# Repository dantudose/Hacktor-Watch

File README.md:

# Hacktor-Watch 2.0

Open-source power for apps, AI, and fearless hardware hacking!
Why just wear a smartwatch when you can hack it? Hacktor Watch 2.0 is your open-source playground on the wrist — powered by the dual-core ESP32-S3 with Wi-Fi and Bluetooth, rocking a bright 1.28" touch display, and loaded with goodies like a 6-axis IMU, mic, speaker, haptics, and fuel gauge. You get 32MB flash, 8MB PSRAM, USB-C charging, and a 200mAh LiPo to keep your creations running. Whether you’re building custom apps in Arduino or ESP-IDF, training tiny AI models, or turning it into a wearable IoT gadget, this is a smartwatch that’s down for any experiment you throw at it. 

And yes — it’s also sleek and stylish, so no matter how good or bad your code is, it will always look great on your wrist!

<div style='float:center'>
   
  </div>

## Hardware Diagram &amp; features

<a href="https://docs.google.com/drawings/d/1u0_o-W6L3w2xveMWQQGLrzZhusZ90oDN8ES3exkrWA4/edit?usp=sharing">Hardware diagram.</a>

This is a open-hardware wearable based on the ESP32 microcontroller. It is fully Arduino-compatible and it comes with the following features:
* <a href="https://www.espressif.com/sites/default/files/documentation/esp32-s3_datasheet_en.pdf">ESP32-S3</a> processor (dual-core 240MHz, WiFI, BLE, 512kB SRAM and 4MB Flash)
* <a href="https://www.aliexpress.com/item/1005007293053050.html">GC9A01</a> 1.28 inch color LCD, 240 x 240 pixels with CST816T capacitive touch screen
* <a href="https://www.st.com/en/mems-and-sensors/lsm6dsl.html">LSM6DSLTR</a> 6-axis inertial sensor (accelerometer and gyroscope)
* <a href="https://www.winbond.com/hq/product/code-storage-flash-memory/serial-nor-flash/?__locale=en&partNo=W25Q256JV">W25Q256JVEIQ</a> 32MB external SPI Flash
* <a href="https://cdn-shop.adafruit.com/product-files/4677/4677_esp-psram64_esp-psram64h_datasheet_en.pdf">ESP-PSRAM64H</a> 8MB PSRAM
* <a href="https://www.ti.com/product/DRV2605/part-details/DRV2605YZFR">DRV2605YZFR</a> haptic driver
* <a href="https://jlcpcb.com/api/file/downloadByFileSystemAccessId/8586212537977618432">LMD2718T261-OA1</a> microphone
* <a href="https://www.analog.com/media/en/technical-documentation/data-sheets/max98357a-max98357b.pdf">MAX98357</a> I2S audio amplifier and speaker
* <a href="https://www.analog.com/media/en/technical-documentation/data-sheets/max17048-max17049.pdf">MAX17048</a> fuel gauge
* Dual <a href="https://www.richtek.com/m/Products/Switching%20Regulators/Buck-Boost%20Converter/RT6160A?sc_lang=en">RT6160</a> DC/DC PMIC (main power and peripherals)
* <a href="https://www.ti.com/lit/ds/symlink/bq24040.pdf?ts=1754753213993">BQ24040</a> LiPo charger
* 200mAh LiPo battery
* USB-C connector for charging and data

<div id="cover">

</div>

## Repository Contents

* **/Hardware** - Schematic and hardware design files (Fusion360 & KiCAD)
* **/Images** - Images & diagrams
* **/Mechanical** - 3D files for the watch case

### Button Layout

 <div style='float:left'>
<table>
<thead>
  <tr>
    <th>Button</th>
    <th>ESP32 Pin</th>
  </tr></thead>
  <tbody>
  <tr>
    <td>BOOT</td>
    <td>IO0</td>
  </tr>
  <tr>
    <td>RESET</td>
    <td>EN</td>
  </tr>
  </tbody>
</table>
 </div>
<div style='float:right'>
   
  </div>

## Software Support
The watch supports Arduino and ESP-IDF programming. For a working NuttX port, check out <a href="https://github.com/radupascale/hectorwatch-nuttx">Radu Pascale's</a> repo. 

## License Information

HW design by <a href="https://github.com/radupascale">Radu Pascale</a>.

This product is _**open source**_! 

Please review the LICENSE file for license information. 

Distributed as-is; no warranty is given.

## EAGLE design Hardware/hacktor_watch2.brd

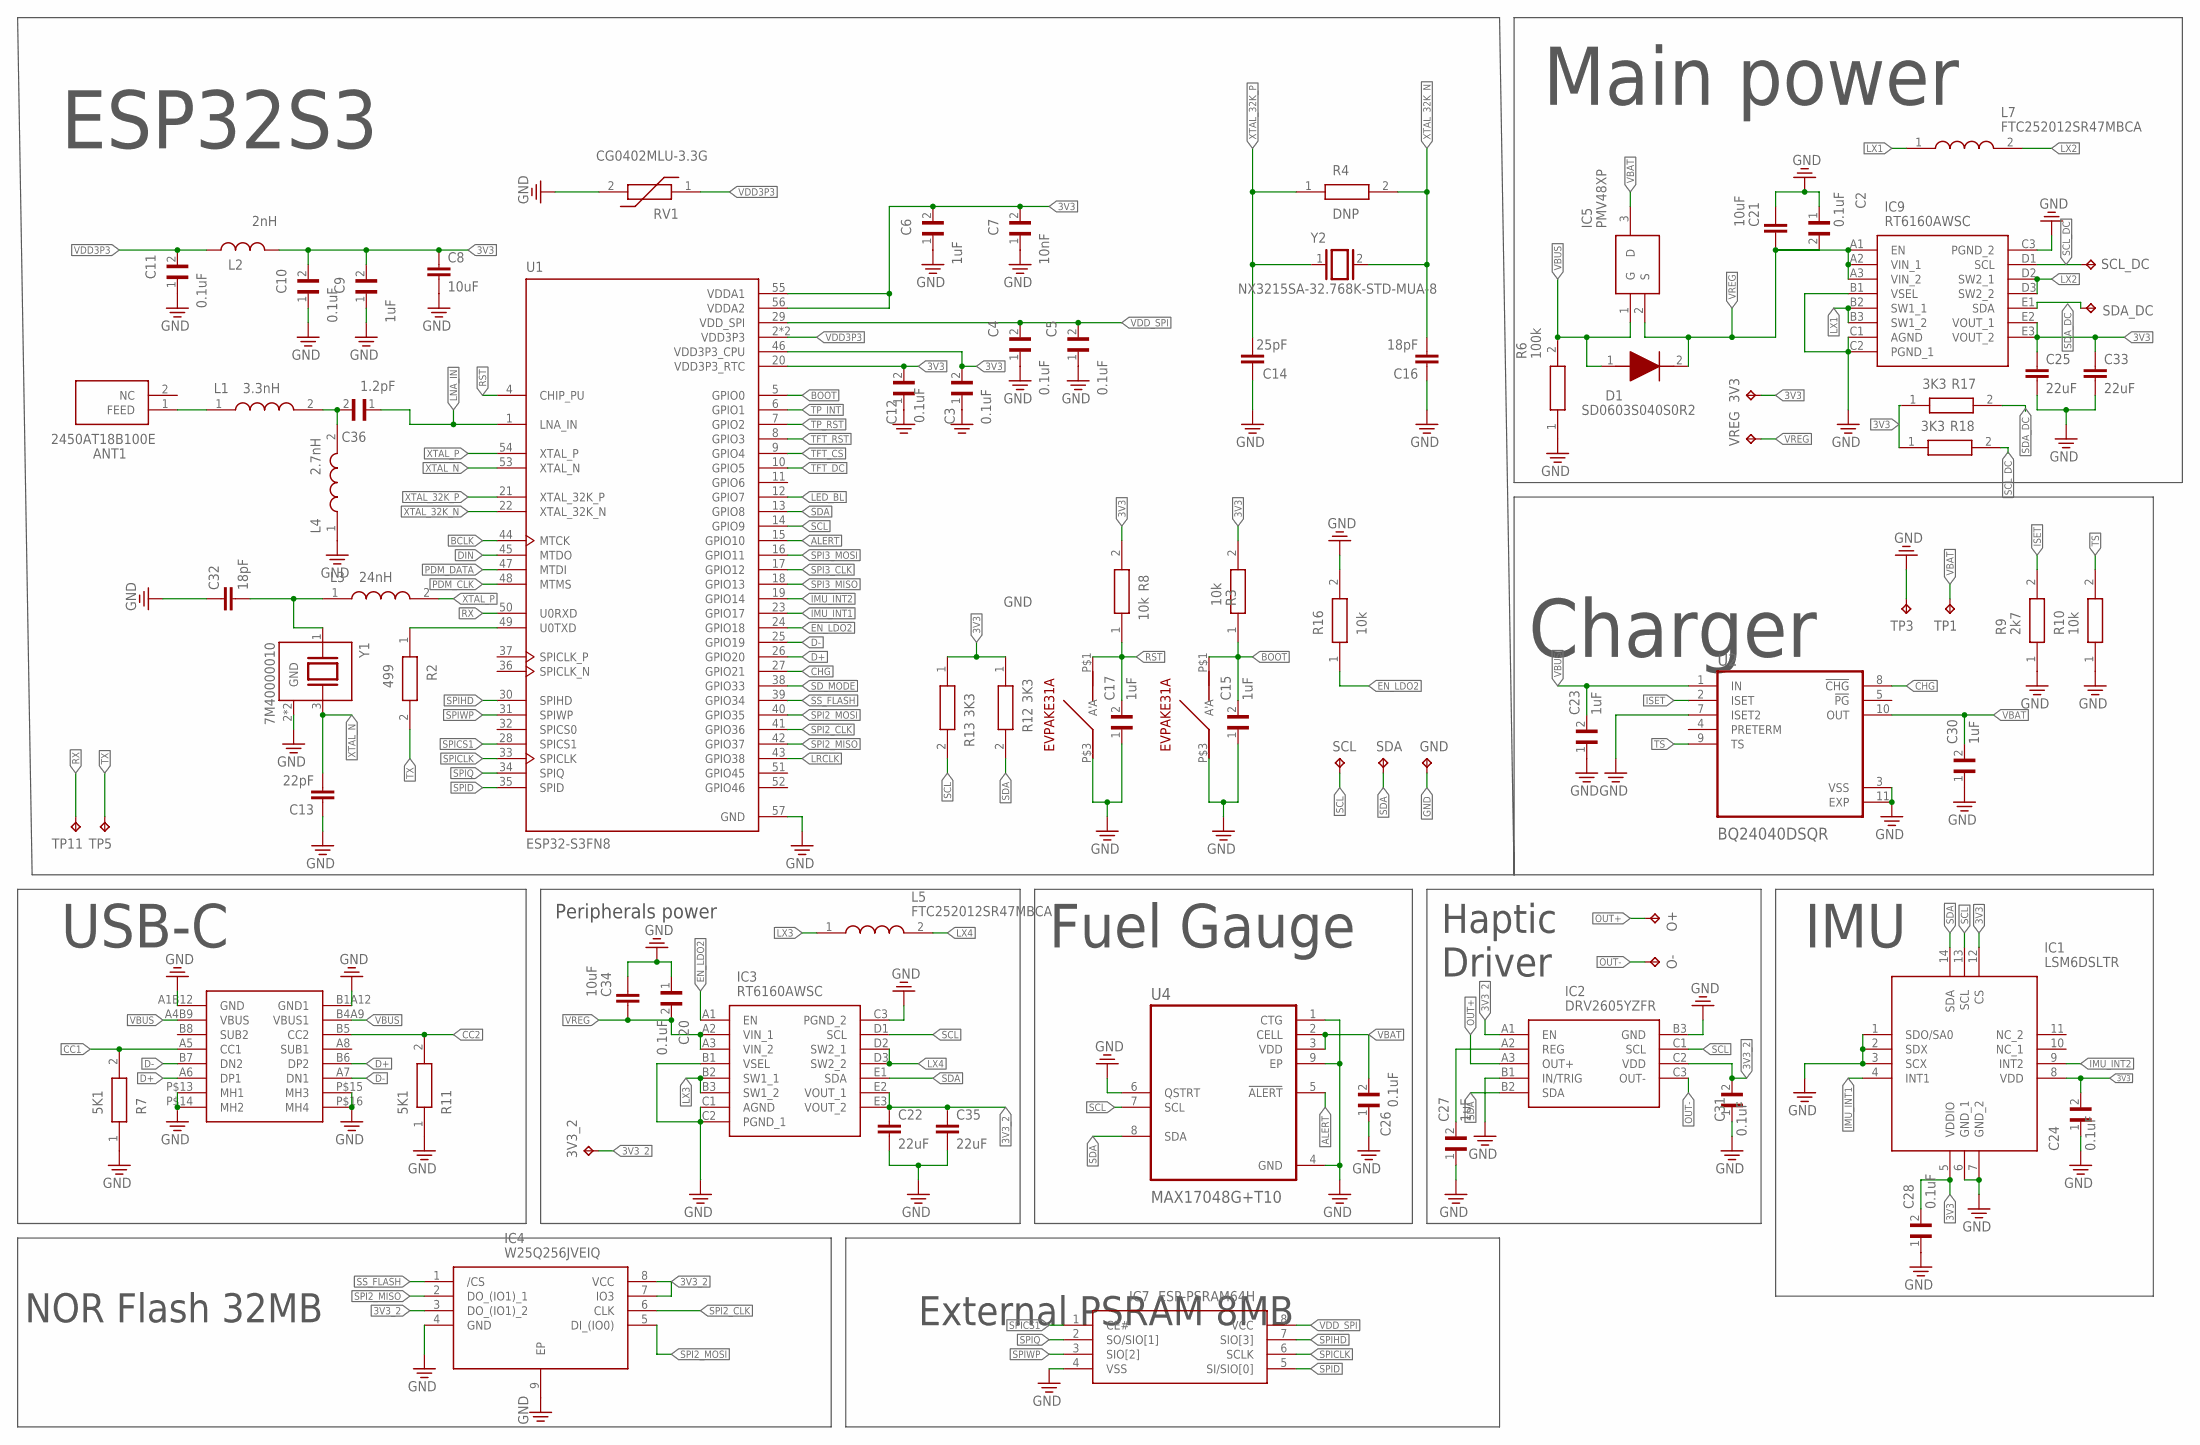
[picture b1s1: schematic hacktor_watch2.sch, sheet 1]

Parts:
3V3, 3V3_2: TPTP20R; TP20R
ANT1: 2450AT18B100E; ANTC3216X140N
C2, C3, C4, C5, C10, C11, C12, C20, C24, C26, C28, C31: 0.1uF; 0201
C6, C9, C15, C17, C23, C27, C30: 1uF; 0201
C7: 10nF; 0201
C8, C21, C34: 10uF; 0402
C13: 22pF; 0402
C14: 25pF; 0402
C16, C32: 18pF; 0402
C22, C25, C33, C35: 22uF; 0402
C36: 1.2pF; 0201
D1: SD0603S040S0R2; SD0603
GND: TPTP20R; TP20R
IC1: LSM6DSLTR
IC2: DRV2605YZFR; BGA9C50P3X3_144X144X62
IC3, IC9: RT6160AWSC; BGA15C40P3X5_140X230X60
IC4: W25Q256JVEIQ; SON127P800X600X80-9N
IC5: PMV48XP; SOT95P230X110-3N
IC7: ESP-PSRAM64H; SOIC127P600X175-8N
L1: 3.3nH; LQP15MN10NG02D
L2: 2nH; INDC1006X60N
L3: 24nH; LQP15MN10NG02D
L4: 2.7nH; LQP15MN10NG02D
L5, L7: FTC252012SR47MBCA; INDC2016X100N
O+: TPTP20R; TP20R
O-: TPTP20R; TP20R
R2: 499; 0201
R3, R8, R10, R16: 10k; 0201
R4: DNP; 0201
R6: 100k; 0201
R7, R11: 5K1; 0201
R9: 2k7; 0201
R12, R13, R17, R18: 3K3; 0201
RV1: CG0402MLU-3.3G; VARC1005X41N
SCL: TPTP20R; TP20R
SCL_DC: TPTP20R; TP20R
SDA: TPTP20R; TP20R
SDA_DC: TPTP20R; TP20R
TP1, TP3, TP5, TP11: TPTP20R; TP20R
U1: ESP32-S3FN8; QFN40P700X700X90-57N
U2: BQ24040DSQR; SON40P200X200X80-11N
U4: MAX17048G+T10; SON50P200X200X80-9N
U$1, U$3: EVPAKE31A
U$5: TYPE-C16PCB0.8073
VREG: TPTP20R; TP20R
Y1: 7M40000010; XTAL_7M40000010
Y2: NX3215SA-32.768K-STD-MUA-8; XTAL_NX3215SA-32.768K-STD-MUA-8

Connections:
3V3: 3V3.TP, C3.2, C6.2, C7.2, C8.1, C9.2, C10.2, C12.2, C24.2, C25.1, C28.2, C33.1, IC1.5 (VDDIO), IC1.8 (VDD), IC1.12 (CS), IC9.E2 (VOUT_1), IC9.E3 (VOUT_2), L2.2, R3.2, R8.2, R12.1, R13.1, R17.1, R18.1, U1.20 (VDD3P3_RTC), U1.46 (VDD3P3_CPU), U1.55 (VDDA1), U1.56 (VDDA2)
3V3_2: 3V3_2.TP, C22.1, C31.2, C35.1, IC2.A1 (EN), IC2.C2 (VDD), IC3.E2 (VOUT_1), IC3.E3 (VOUT_2), IC4.3 (DO_(IO1)_2), IC4.7 (IO3), IC4.8 (VCC); also elsewhere on the board
ALERT: U1.15 (GPIO10), U4.5 (!ALERT)
BCLK: U1.44 (MTCK); also elsewhere on the board
BOOT: C15.2, R3.1, U1.5 (GPIO0), U$1.P$1 (A)
CC1: R7.2, U$5.A5 (CC1)
CC2: R11.2, U$5.B5 (CC2)
CHG: U1.27 (GPIO21), U2.8 (!CHG)
D+: U1.26 (GPIO20), U$5.A6 (DP1), U$5.B6 (DP2)
D-: U1.25 (GPIO19), U$5.A7 (DN1), U$5.B7 (DN2)
DIN: U1.45 (MTDO); also elsewhere on the board
EN_LDO2: IC3.A1 (EN), R16.1, U1.24 (GPIO18)
GND: C2.1, C3.1, C4.1, C5.1, C6.1, C7.1, C8.2, C9.1, C10.1, C11.1, C12.1, C13.1, C14.1, C15.1, C16.1, C17.1, C20.1, C21.1, C22.2, C23.1, C24.1, C25.2, C26.1, C27.1, C28.1, C30.1, C31.1, C32.1, C33.2, C34.1, C35.2, GND.TP, IC1.1 (SDO/SA0), IC1.2 (SDX), IC1.3 (SCX), IC1.6 (GND_1), IC1.7 (GND_2), IC2.B1 (IN/TRIG), IC2.B3 (GND), IC3.B1 (VSEL), IC3.C1 (AGND), IC3.C2 (PGND_1), IC3.C3 (PGND_2), IC4.4 (GND), IC4.9 (EP), IC7.4 (VSS), IC9.B1 (VSEL), IC9.C1 (AGND), IC9.C2 (PGND_1), IC9.C3 (PGND_2), L4.1, R6.1, R7.1, R9.1, R10.1, R11.1, R16.2, RV1.2, TP3.TP, U1.57 (GND), U2.3 (VSS), U2.7 (ISET2), U2.11 (EXP), U4.1 (CTG), U4.4 (GND), U4.6 (QSTRT), U4.9 (EP), U$1.P$3 (A'), U$3.P$3 (A'), U$5.A1B12 (GND), U$5.B1A12 (GND1), U$5.P$13 (MH1), U$5.P$14 (MH2), U$5.P$15 (MH3), U$5.P$16 (MH4), Y1.2 (GND), Y1.4 (GND); also elsewhere on the board
IMU_INT1: IC1.4 (INT1), U1.23 (GPIO17)
IMU_INT2: IC1.9 (INT2), U1.19 (GPIO14)
ISET: R9.2, U2.2 (ISET)
LED_BL: U1.12 (GPIO7); also elsewhere on the board
LNA_IN: C36.1, U1.1 (LNA_IN)
LRCLK: U1.43 (GPIO38); also elsewhere on the board
LX1: IC9.B2 (SW1_1), IC9.B3 (SW1_2), L7.1
LX2: IC9.D2 (SW2_1), IC9.D3 (SW2_2), L7.2
LX3: IC3.B2 (SW1_1), IC3.B3 (SW1_2), L5.1
LX4: IC3.D2 (SW2_1), IC3.D3 (SW2_2), L5.2
unnamed: C32.2, L3.1, Y1.1
unnamed: ANT1.1 (FEED), L1.1
unnamed: C36.2, L1.2, L4.2
unnamed: R2.1, U1.49 (U0TXD)
unnamed: C27.2, IC2.A2 (REG)
OUT+: IC2.A3 (OUT+), O+.TP
OUT-: IC2.C3 (OUT-), O-.TP
PDM_CLK: U1.48 (MTMS); also elsewhere on the board
PDM_DATA: U1.47 (MTDI); also elsewhere on the board
RST: C17.2, R8.1, U1.4 (CHIP_PU), U$3.P$1 (A)
RX: TP11.TP, U1.50 (U0RXD)
SCL: IC1.13 (SCL), IC2.C1 (SCL), IC3.D1 (SCL), R13.2, SCL.TP, U1.14 (GPIO9), U4.7 (SCL); also elsewhere on the board
SCL_DC: IC9.D1 (SCL), R18.2, SCL_DC.TP
SDA: IC1.14 (SDA), IC2.B2 (SDA), IC3.E1 (SDA), R12.2, SDA.TP, U1.13 (GPIO8), U4.8 (SDA); also elsewhere on the board
SDA_DC: IC9.E1 (SDA), R17.2, SDA_DC.TP
SD_MODE: U1.38 (GPIO33); also elsewhere on the board
SPI2_CLK: IC4.6 (CLK), U1.41 (GPIO36)
SPI2_MISO: IC4.2 (DO_(IO1)_1), U1.42 (GPIO37)
SPI2_MOSI: IC4.5 (DI_(IO0)), U1.40 (GPIO35)
SPI3_CLK: U1.17 (GPIO12); also elsewhere on the board
SPI3_MISO: U1.18 (GPIO13)
SPI3_MOSI: U1.16 (GPIO11); also elsewhere on the board
SPICLK: IC7.6 (SCLK), U1.33 (SPICLK)
SPICS1: IC7.1 (CE#), U1.28 (SPICS1)
SPID: IC7.5 (SI/SIO[0]), U1.35 (SPID)
SPIHD: IC7.7 (SIO[3]), U1.30 (SPIHD)
SPIQ: IC7.2 (SO/SIO[1]), U1.34 (SPIQ)
SPIWP: IC7.3 (SIO[2]), U1.31 (SPIWP)
SS_FLASH: IC4.1 (/CS), U1.39 (GPIO34)
TFT_CS: U1.9 (GPIO4); also elsewhere on the board
TFT_DC: U1.10 (GPIO5); also elsewhere on the board
TFT_RST: U1.8 (GPIO3); also elsewhere on the board
TP_INT: U1.6 (GPIO1); also elsewhere on the board
TP_RST: U1.7 (GPIO2); also elsewhere on the board
TS: R10.2, U2.9 (TS)
TX: R2.2, TP5.TP
VBAT: C26.2, C30.2, IC5.3 (D), TP1.TP, U2.10 (OUT), U4.2 (CELL), U4.3 (VDD)
VBUS: C23.2, D1.1 (A), IC5.1 (G), R6.2, U2.1 (IN), U$5.A4B9 (VBUS), U$5.B4A9 (VBUS1)
VDD3P3: C11.2, L2.1, RV1.1, U1.2 (VDD3P3), U1.3 (VDD3P3)
VDD_SPI: C4.2, C5.2, IC7.8 (VCC), U1.29 (VDD_SPI)
VREG: C2.2, C20.2, C21.2, C34.2, D1.2 (K), IC3.A2 (VIN_1), IC3.A3 (VIN_2), IC5.2 (S), IC9.A1 (EN), IC9.A2 (VIN_1), IC9.A3 (VIN_2), VREG.TP
XTAL_32K_N: C16.2, R4.2, U1.22 (XTAL_32K_N), Y2.2
XTAL_32K_P: C14.2, R4.1, U1.21 (XTAL_32K_P), Y2.1
XTAL_N: C13.2, U1.53 (XTAL_N), Y1.3 (2)
XTAL_P: L3.2, U1.54 (XTAL_P)

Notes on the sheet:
ESP32S3
Main power
Charger
USB-C
Peripherals power
Fuel Gauge
IMU
Haptic Driver
NOR Flash 32MB
External PSRAM 8MB

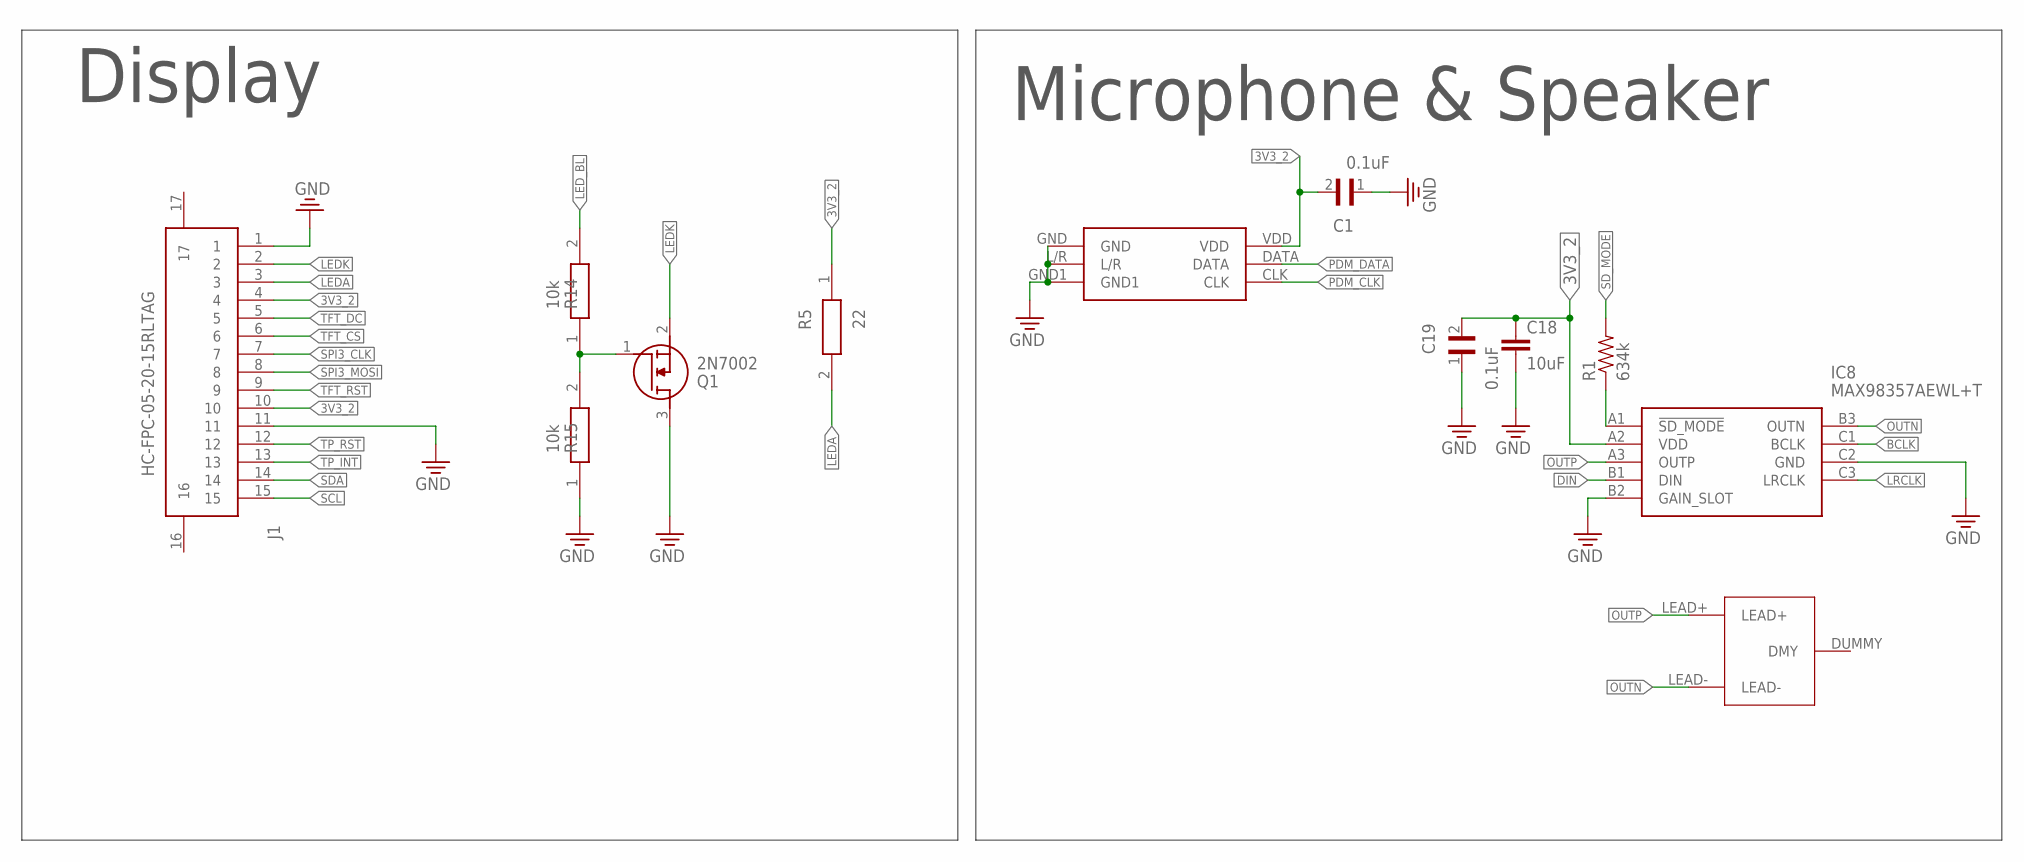
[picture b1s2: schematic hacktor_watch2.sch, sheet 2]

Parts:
C1, C19: 0.1uF; 0201
C18: 10uF; 0402
IC8: MAX98357AEWL+T; BGA9C40P3X3_144X135X69
J1: HC-FPC-05-20-15RLTAG
Q1: 2N7002; SOT96P240X120-3N
R1: 634k; 0402
R5: 22; 0201
R14, R15: 10k; 0201
U$4: TE054003-1
U$6: LMD2718T261-OA1

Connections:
3V3_2: C1.2, C18.1, C19.2, IC8.A2 (VDD), J1.4, J1.10, R5.1, U$6.VDD; also elsewhere on the board
BCLK: IC8.C1 (BCLK); also elsewhere on the board
DIN: IC8.B1 (DIN); also elsewhere on the board
GND: C1.1, C18.2, C19.1, IC8.B2 (GAIN_SLOT), IC8.C2 (GND), J1.1, J1.11, Q1.3 (D), R15.1, U$6.GND, U$6.GND1, U$6.L/R; also elsewhere on the board
LEDA: J1.3, R5.2
LEDK: J1.2, Q1.2 (S)
LED_BL: R14.2; also elsewhere on the board
LRCLK: IC8.C3 (LRCLK); also elsewhere on the board
unnamed: IC8.A1 (!SD_MODE), R1.1
unnamed: Q1.1 (G), R14.1, R15.2
OUTN: IC8.B3 (OUTN), U$4.LEAD-
OUTP: IC8.A3 (OUTP), U$4.LEAD+
PDM_CLK: U$6.CLK; also elsewhere on the board
PDM_DATA: U$6.DATA; also elsewhere on the board
SCL: J1.15; also elsewhere on the board
SDA: J1.14; also elsewhere on the board
SD_MODE: R1.2; also elsewhere on the board
SPI3_CLK: J1.7; also elsewhere on the board
SPI3_MOSI: J1.8; also elsewhere on the board
TFT_CS: J1.6; also elsewhere on the board
TFT_DC: J1.5; also elsewhere on the board
TFT_RST: J1.9; also elsewhere on the board
TP_INT: J1.13; also elsewhere on the board
TP_RST: J1.12; also elsewhere on the board

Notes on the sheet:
Display
Microphone & Speaker

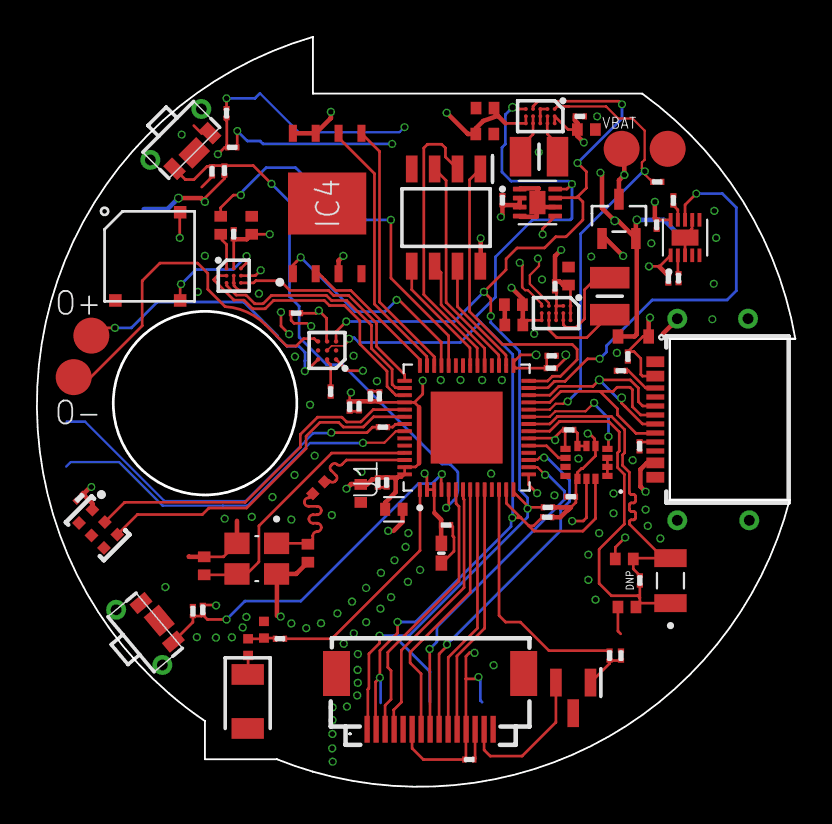
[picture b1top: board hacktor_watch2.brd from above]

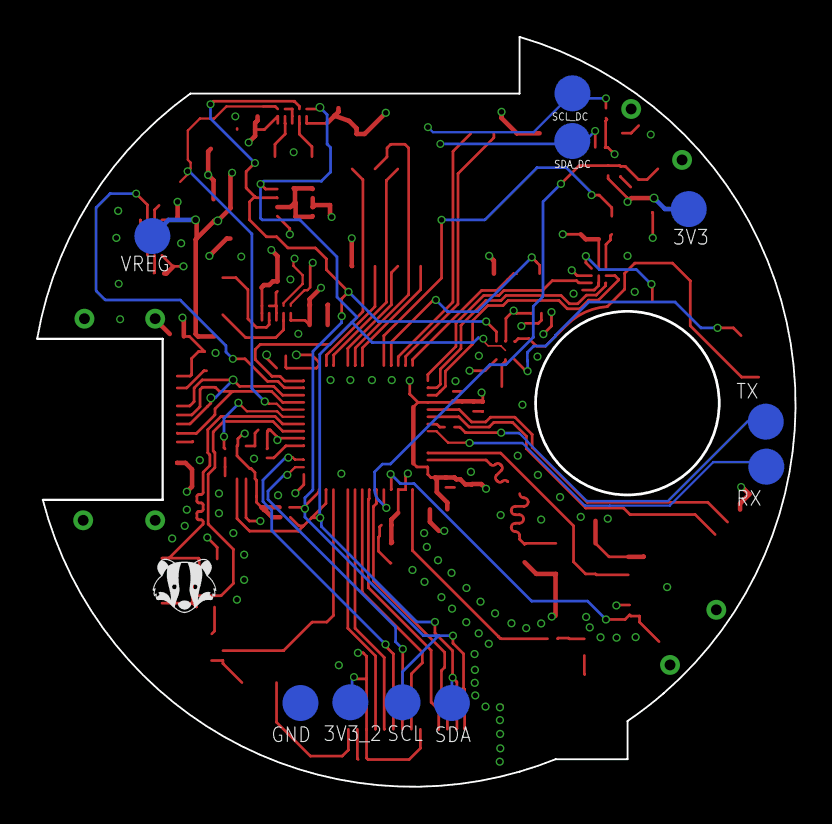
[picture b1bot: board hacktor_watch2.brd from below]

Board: 4 copper layers, 42.1 x 41.7 mm, 96 parts (10 on the bottom side), 73 nets.

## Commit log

2025-08-09 Update and rename readme to ReadMe
